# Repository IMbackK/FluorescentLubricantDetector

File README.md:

# Fluorescent lubricant detector

This is the hardware to a lubricant detection system that uses flurecent indecator materials to detect the thikness of lubricants on arbitrary surfaces.
It performs image detection and undistrotion of the surface under test, lighting and angle correction as well as the application of callibration curves to aquire accurate thikness data in a fast and non-contact fashion.

Hardware wise this is implemented using a integrating sphere to light an object under test evenly with a known irradiance and subsequently aquireing the surface of the object under test using a four cameras.

- The implentaton of the algorithums used can be found in this shared libary: https://gitlab.com/CKCSGLA/uvowunwrap
- The camera interface can be found here: https://gitlab.com/CKCSGLA/uvoscam
- A Gui frontend for this system can be found here: https://gitlab.com/CKCSGLA/LubricantThicknessMapper

- The LedController directory contains the design of and the kicad files for a usb attached led contoller board with linear regulation and camera triggering.
	-  Kicad can be found here: https://www.kicad.org/
- The LedPcb directory contains the design of and the kicad files for a mechanical adapter board for the LED packages to be used with the LedController PCB.
- IntegratingSphere contains CAD fils for the mechanical setup of the integrating sphere and the assoicated equipment.

License: CC BY-SA 2.0, see https://creativecommons.org/licenses/by-sa/2.0/legalcode

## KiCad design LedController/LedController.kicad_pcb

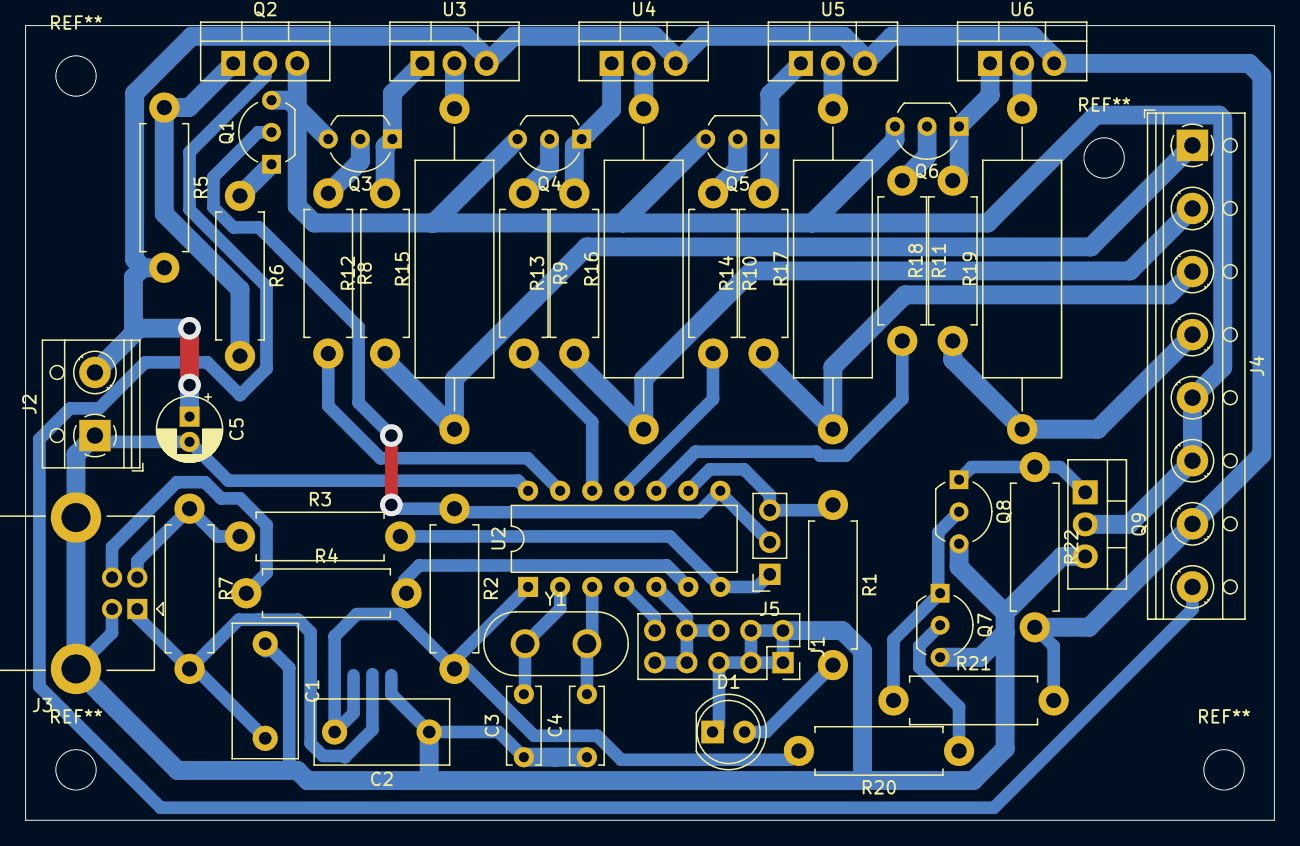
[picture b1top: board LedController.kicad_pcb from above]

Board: 2 copper layers, 99.0 x 63.0 mm, 49 parts (1 on the bottom side), 42 nets.

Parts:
C1, C2: C; C_Disc_D10.5mm_W5.0mm_P7.50mm
C3, C4: C; C_Disc_D6.0mm_W2.5mm_P5.00mm
C5: CP; CP_Radial_D5.0mm_P2.00mm
D1: LED; LED_D5.0mm
J1: Conn_02x05; PinSocket_2x05_P2.54mm_Vertical
J2: Screw_Terminal_01x02; TerminalBlock_RND_205-00012_1x02_P5.00mm_Horizontal
J3: USB_B; USB_B_Lumberg_2411_02_Horizontal
J4: Screw_Terminal_01x08; TerminalBlock_RND_205-00018_1x08_P5.00mm_Horizontal
J5: Conn_01x03_Male; PinSocket_1x03_P2.54mm_Vertical
Q1, Q3, Q4, Q5, Q6, Q7, Q8: BC337; TO-92_Inline_Wide
Q2, Q9: IRF3205; TO-220-3_Vertical
R1: 330R; R_Axial_DIN0411_L9.9mm_D3.6mm_P12.70mm_Horizontal
R2, R8, R9, R10, R11: 1K; R_Axial_DIN0411_L9.9mm_D3.6mm_P12.70mm_Horizontal
R3, R4: 68R; R_Axial_DIN0411_L9.9mm_D3.6mm_P12.70mm_Horizontal
R5, R20, R22: 4.7K; R_Axial_DIN0411_L9.9mm_D3.6mm_P12.70mm_Horizontal
R6: 100R; R_Axial_DIN0411_L9.9mm_D3.6mm_P12.70mm_Horizontal
R7: 1.5K; R_Axial_DIN0411_L9.9mm_D3.6mm_P12.70mm_Horizontal
R12, R13, R14, R18: 1.8K; R_Axial_DIN0411_L9.9mm_D3.6mm_P12.70mm_Horizontal
R15, R16, R17, R19: 1R; R_Axial_DIN0617_L17.0mm_D6.0mm_P25.40mm_Horizontal
R21: 100K; R_Axial_DIN0411_L9.9mm_D3.6mm_P12.70mm_Horizontal
U1: HT75xx-1-SOT89; SOT-89-3
U2: ATtiny44-20PU; DIP-14_W7.62mm
U3, U4, U5, U6: LM317_TO-220; TO-220-3_Vertical
Y1: 12M; Crystal_HC50_Vertical

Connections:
+5V: C1.2, J3.1, R7.2, U1.2
+12V: C5.1, J2.2, J4.7, R5.2, R21.2, R22.2, U3.3, U4.3, U5.3, U6.3
GND: C1.1, C2.1, C3.1, C4.1, C5.2, D1.1, J1.1, J1.2, J1.3, J1.4, J1.5, J2.1, J3.4, J3.5, Q7.3, Q8.3, Q9.3, U1.1, U2.14
GND2: J4.5, J4.6, Q1.3, Q2.3, Q3.3, Q4.3, Q5.3, Q6.3, Q9.2
unnamed: C3.2, U2.2, Y1.1
unnamed: C4.2, U2.3, Y1.2
unnamed: D1.2, R1.2
unnamed: J1.6, J1.7, J1.8, J1.9, U2.5
unnamed: J1.10, U2.4
unnamed: J3.2, R3.1, R7.1
unnamed: J3.3, R4.1
unnamed: J4.1, R12.1, R15.1
unnamed: J4.2, R13.1, R16.1
unnamed: J4.3, R14.1, R17.1
unnamed: J4.4, R18.1, R19.1
unnamed: J4.8, Q2.2
unnamed: J5.1, R3.2, U2.7
unnamed: J5.2, Q1.2, R2.1, U2.8
unnamed: J5.3, R1.1, U2.9
unnamed: Q1.1, R6.1
unnamed: Q2.1, R5.1, R6.2
unnamed: Q3.1, R12.2, U3.1
unnamed: Q3.2, R8.1
unnamed: Q4.1, R13.2, U4.1
unnamed: Q4.2, R9.1
unnamed: Q5.1, R14.2, U5.1
unnamed: Q5.2, R10.1
unnamed: Q6.1, R18.2, U6.1
unnamed: Q6.2, R11.1
unnamed: Q7.1, Q8.2, R21.1
unnamed: Q7.2, R20.1
unnamed: Q8.1, Q9.1, R22.1
unnamed: R4.2, U2.6
unnamed: R8.2, U2.13
unnamed: R9.2, U2.12
unnamed: R10.2, U2.11
unnamed: R11.2, U2.10
unnamed: R15.2, U3.2
unnamed: R16.2, U4.2
unnamed: R17.2, U5.2
unnamed: R19.2, U6.2
VCC: C2.2, R2.2, R20.2, U1.3, U2.1

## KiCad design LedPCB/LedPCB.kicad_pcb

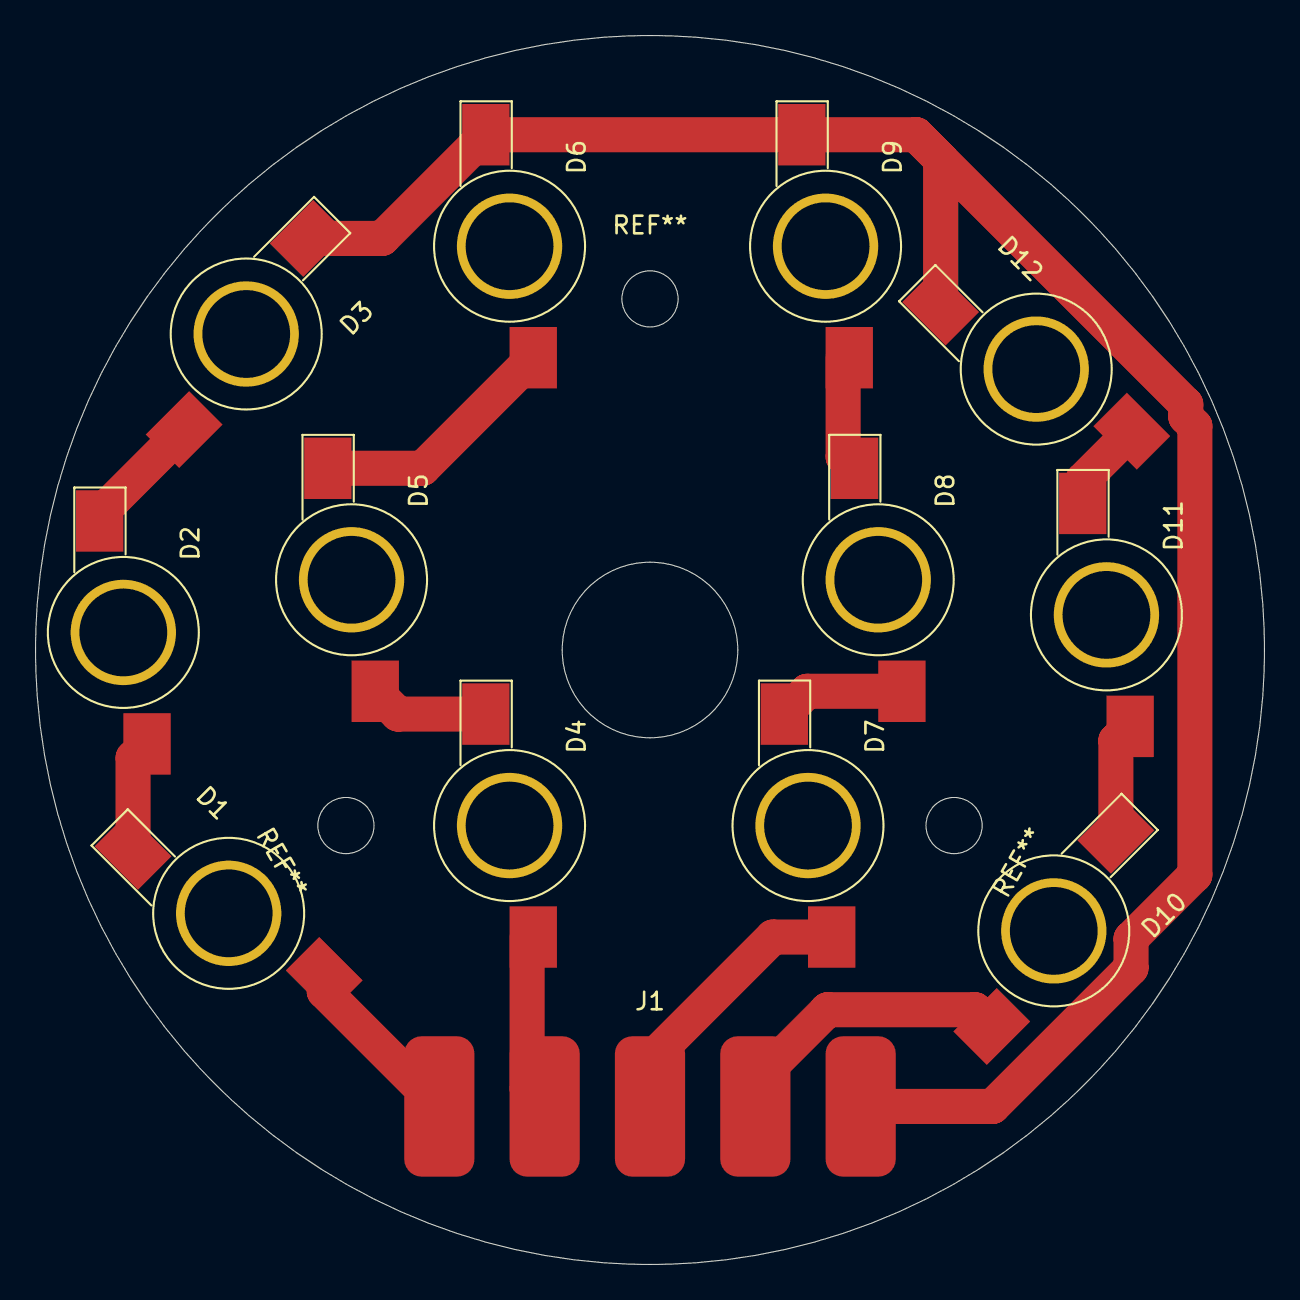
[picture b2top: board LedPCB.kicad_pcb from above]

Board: 2 copper layers, 70.0 x 70.0 mm, 13 parts (0 on the bottom side), 13 nets.

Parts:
D1, D2, D3, D4, D5, D6, D7, D8, D9, D10, D11, D12: LED; LED_1W_3W_R8_hole
J1: Conn_01x05_Male; WireSolderingPad5

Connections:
GND: D3.1, D6.1, D9.1, D12.1, J1.1
unnamed: D1.1, D2.2
unnamed: D1.2, J1.5
unnamed: D2.1, D3.2
unnamed: D4.1, D5.2
unnamed: D4.2, J1.4
unnamed: D5.1, D6.2
unnamed: D7.1, D8.2
unnamed: D7.2, J1.3
unnamed: D8.1, D9.2
unnamed: D10.1, D11.2
unnamed: D10.2, J1.2
unnamed: D11.1, D12.2

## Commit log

2021-11-20 Inital commit
